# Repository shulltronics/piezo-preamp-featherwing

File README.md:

Piezo Preamp FeatherWing
=========================================

### By Carsten Thue-Bludworth, September 2024

This featherwing provides a high-impedance gain stage and a simple envelope follower for piezo contact microphones.

The piezo is connected via a standard 3.5mm TRS shielded audio connector with the following pinout:
 - Tip: piezo signal
 - Ring: piezo ground
 - Sleeve: cable shield (not connected on piezo end)

The board requires a bipolar +12V/-12V power supply, provided via a 4pos Molex SL connector with the following pinout:
 - 1: +12V
 - 2: GND
 - 3: -12V
 - 4: signal out (default to unattenuated envelope follower signal).

Jumpers and plated holes are provided to configure which signals are sent to which pins.
* By default, the SL connector gets the unattenuated envelope follower signal.
* By default, no analog pins on the feather headers are connected. Use wire jumpers to connect signals to the analog pins you want to use.
* Jumpers can configure the amplifier stage gain, as well as the envelope follower decay time. By default, the gain is 100x and the decay is set with a 270k resistor.

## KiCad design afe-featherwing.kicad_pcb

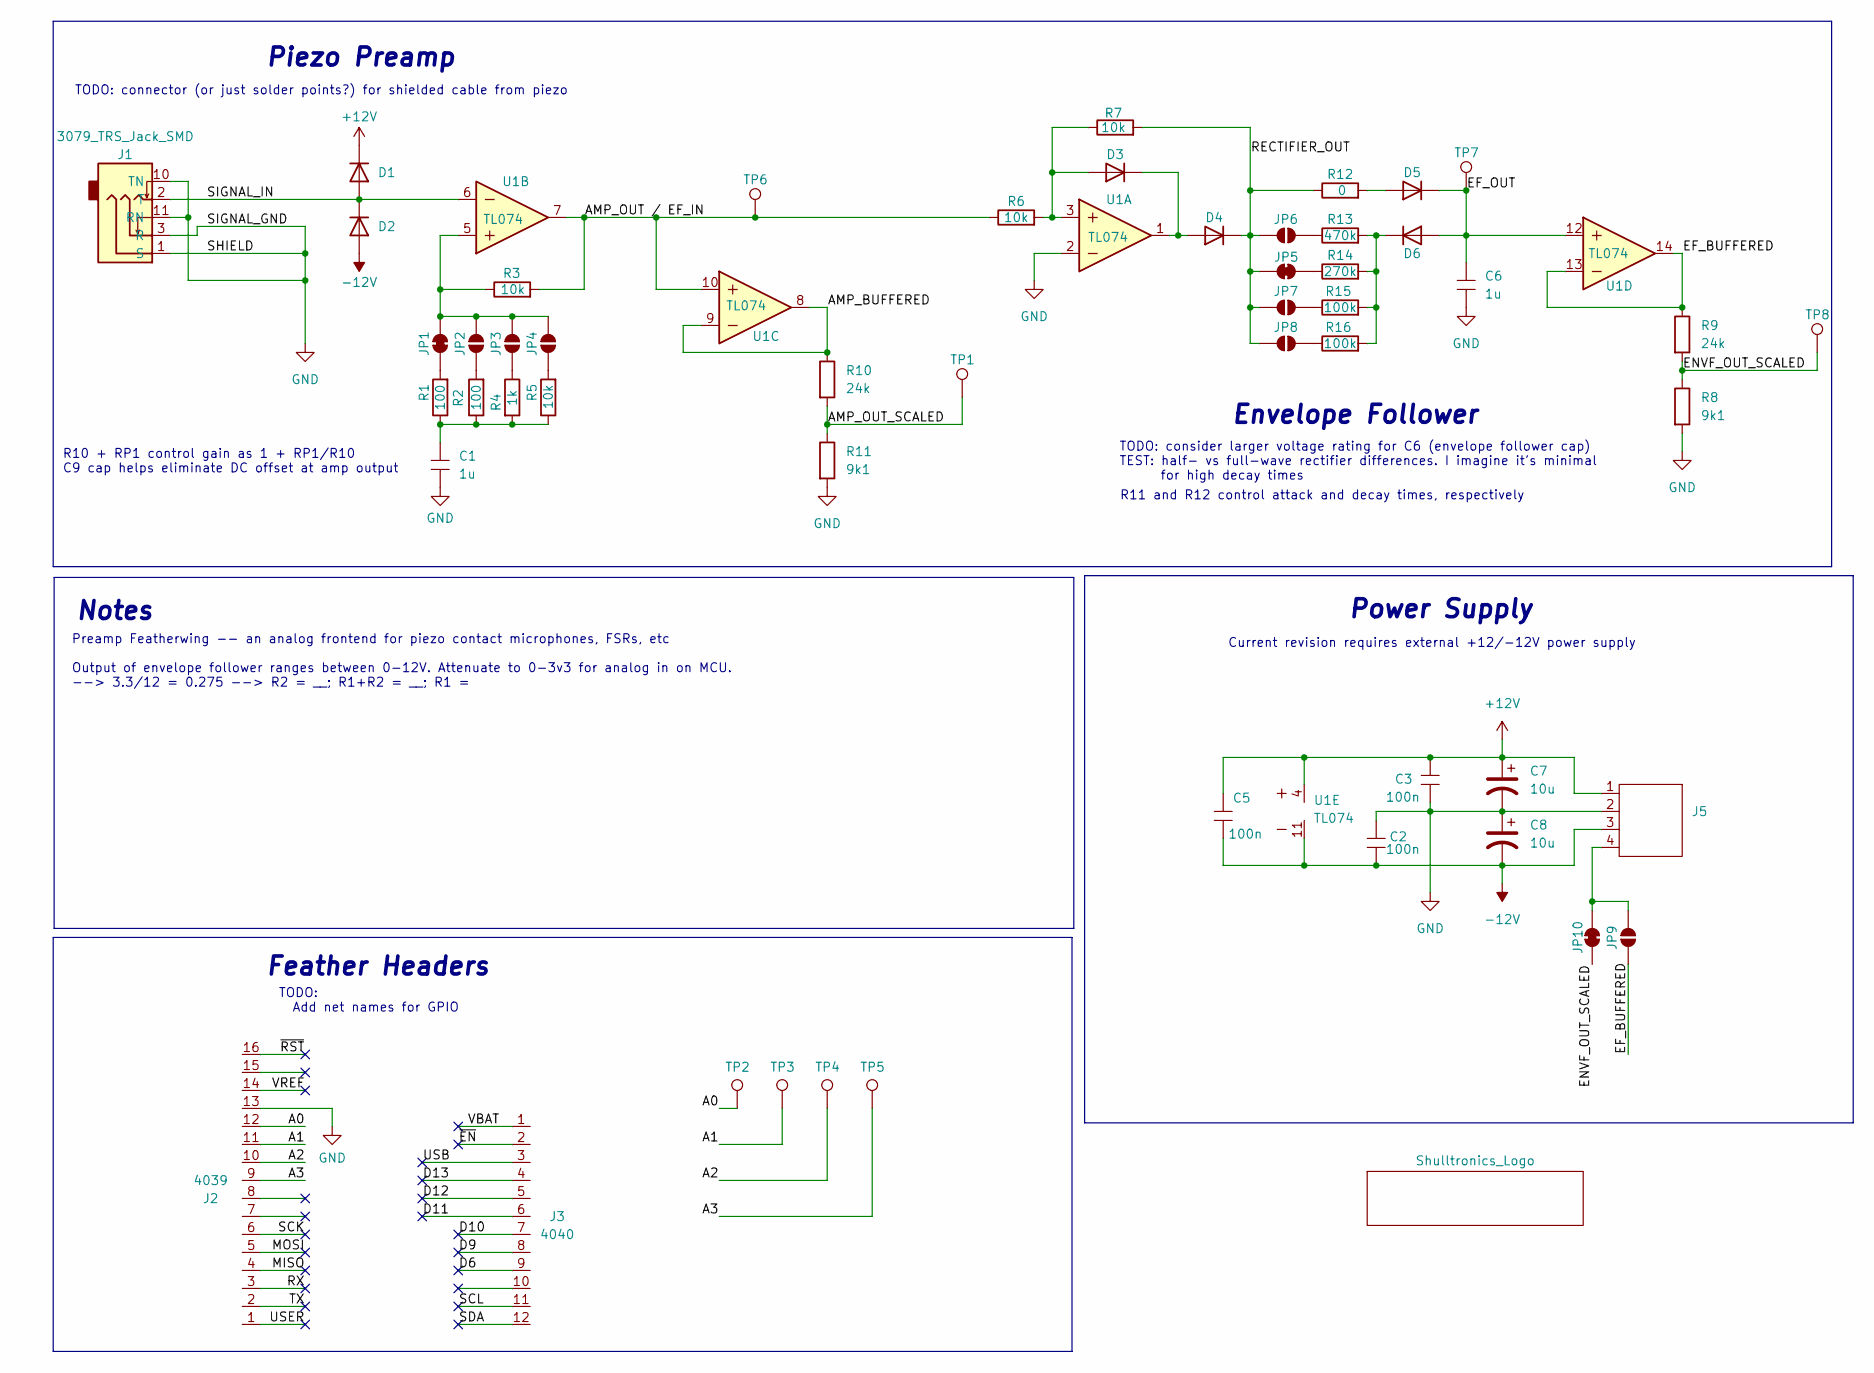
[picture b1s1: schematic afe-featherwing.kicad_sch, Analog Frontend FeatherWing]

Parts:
C1, C6: 4013_Capacitor_1u_16V_0402; C_0402_HandSolder
C2, C3, C5: 3089_Capacitor_100n_16V_0402; C_0402_HandSolder
C7, C8: 4031_Capacitor_10u_35V_SMD; 3088_Capacitor_10u_50V_SMD
D1, D2, D3, D4, D5, D6: 1N4148W; D_SOD-323
J1: 3079_TRS_Jack_SMD
J2: 4039_Header_Male_Vert_16pin_0.1in; 4039_Header_16pos_2.54mm
J3: 4040_Header_Male_Vert_12pin_0.1in; 4040_Header_12pos_2.54mm
J5: 3033_Connector_SL_4pos_RA; 3033_Molex_SL_4pos_RA
JP1: 100; SolderJumper-2_P1.3mm_Bridged_Pad1.0x1.5mm
JP2: 100; SolderJumper-2_P1.3mm_Open_TrianglePad1.0x1.5mm
JP3: 1k; SolderJumper-2_P1.3mm_Open_TrianglePad1.0x1.5mm
JP4: 10k; SolderJumper-2_P1.3mm_Open_TrianglePad1.0x1.5mm
JP5: 270k; SolderJumper-2_P1.3mm_Bridged_Pad1.0x1.5mm
JP6: 470k; SolderJumper-2_P1.3mm_Open_TrianglePad1.0x1.5mm
JP7, JP8: 100k; SolderJumper-2_P1.3mm_Open_TrianglePad1.0x1.5mm
JP9: EF_BUF; SolderJumper-2_P1.3mm_Open_TrianglePad1.0x1.5mm
JP10: EF_ATN; SolderJumper-2_P1.3mm_Bridged_Pad1.0x1.5mm
L1: Shulltronics_Logo
R1, R2: 4038_Resistor_SMD_100_0.125W_1%; RES-0402
R3, R5, R6, R7: 4008_Resistor_SMD_10k_0.125W_1%; RES-0402
R4: 4010_Resistor_SMD_1k_0.125W_1%; RES-0402
R8, R11: 4082_Resistor_SMD_9k1_1/16W_1%; RES-0402
R9, R10: 4083_Resistor_SMD_24k_1/16W_1%; RES-0402
R12: 4021_Resistor_SMD_Jumper; RES-0402
R13: 4080_Resistor_SMD_470k_0.125W_1%; RES-0402
R14: 4019_Resistor_SMD_270k_0.125W_1%; RES-0402
R15, R16: 4017_Resistor_SMD_100k_0.125W_1%_1; RES-0402
TP1: AMP_ATN; TestPoint_THTPad_D1.5mm_Drill0.7mm
TP2: A0; TestPoint_THTPad_D1.5mm_Drill0.7mm
TP3: A1; TestPoint_THTPad_D1.5mm_Drill0.7mm
TP4: A2; TestPoint_THTPad_D1.5mm_Drill0.7mm
TP5: A3; TestPoint_THTPad_D1.5mm_Drill0.7mm
TP6: AMP_OUT; TestPoint_THTPad_D1.5mm_Drill0.7mm
TP7: EF_BUF; TestPoint_THTPad_D1.5mm_Drill0.7mm
TP8: EF_ATN; TestPoint_THTPad_D1.5mm_Drill0.7mm
U1: 3099_TL074CPW_SMD; 3099_TL074CPW_TSSOP14

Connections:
+12V: C3.2, C5.2, C7.1, D1.1 (K), J5.1, U1.4 (VCC)
-12V: C2.1, C5.1, C8.2, D2.2 (A), J5.3, U1.11 (VEE)
/A0: J2.12, TP2.1
/A1: J2.11, TP3.1
/A2: J2.10, TP4.1
/A3: J2.9, TP5.1
/AMP_BUFFERED: R10.1, U1.8 (3OUT), U1.9 (3IN-)
/AMP_OUT / EF_IN: R3.2, R6.1, TP6.1, U1.7 (2OUT), U1.10 (3IN+)
/AMP_OUT_SCALED: R10.2, R11.1, TP1.1
/D6: J3.9
/D9: J3.8
/D10: J3.7
/D11: J3.6
/D12: J3.5
/D13: J3.4
/EF_BUFFERED: JP9.1 (A), R9.1, U1.13 (4IN-), U1.14 (4OUT)
/EF_OUT: C6.2, D5.1 (K), D6.2 (A), TP7.1, U1.12 (4IN+)
/ENVF_OUT_SCALED: JP10.1 (A), R8.1, R9.2, TP8.1
/MISO: J2.4
/MOSI: J2.5
/RECTIFIER_OUT: D4.1 (K), JP5.1 (A), JP6.1 (A), JP7.1 (A), JP8.1 (A), R7.2, R12.1
/RX: J2.3
/SCK: J2.6
/SCL: J3.11
/SDA: J3.12
/SIGNAL_IN: D1.2 (A), D2.1 (K), J1.2 (T), U1.6 (2IN-)
/TX: J2.2
/USB: J3.3
/USER: J2.1
/VBAT: J3.1
/VREF: J2.14
/~EN: J3.2
/~RST: J2.16
GND: C1.1, C2.2, C3.1, C6.1, C7.2, C8.1, J1.1 (S), J1.3 (R), J1.10 (TN), J1.11 (RN), J2.13, J5.2, R8.2, R11.2, U1.2 (1IN-)
unnamed: C1.2, R1.1, R2.1, R4.2, R5.1
unnamed: D3.2 (A), R6.2, R7.1, U1.3 (1IN+)
unnamed: D3.1 (K), D4.2 (A), U1.1 (1OUT)
unnamed: D5.2 (A), R12.2
unnamed: D6.1 (K), R13.2, R14.2, R15.2, R16.2
unnamed: JP1.1 (A), R1.2
unnamed: JP1.2 (B), JP2.2 (B), JP3.2 (B), JP4.2 (B), R3.1, U1.5 (2IN+)
unnamed: JP2.1 (A), R2.2
unnamed: JP3.1 (A), R4.1
unnamed: JP4.1 (A), R5.2
unnamed: JP5.2 (B), R14.1
unnamed: JP6.2 (B), R13.1
unnamed: JP7.2 (B), R15.1
unnamed: JP8.2 (B), R16.1
unnamed: J5.4, JP9.2 (B), JP10.2 (B)

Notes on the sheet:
Notes
TODO: Add net names for GPIO
Envelope Follower
Piezo Preamp
Power Supply
Preamp Featherwing -- an analog frontend for piezo contact microphones, FSRs, etc Output of envelope follower ranges between 0-12V. Attenuate to 0-3v3 for analog in on MCU. --> 3.3/12 = 0.275 --> R2 = __; R1+R2 = __; R1 =
Feather Headers
TODO: consider larger voltage rating for C6 (envelope follower cap) TEST: half- vs full-wave rectifier differences. I imagine it's minimal for high decay times
Current revision requires external +12/-12V power supply
R11 and R12 control attack and decay times, respectively
TODO: connector (or just solder points?) for shielded cable from piezo
R10 + RP1 control gain as 1 + RP1/R10 C9 cap helps eliminate DC offset at amp output

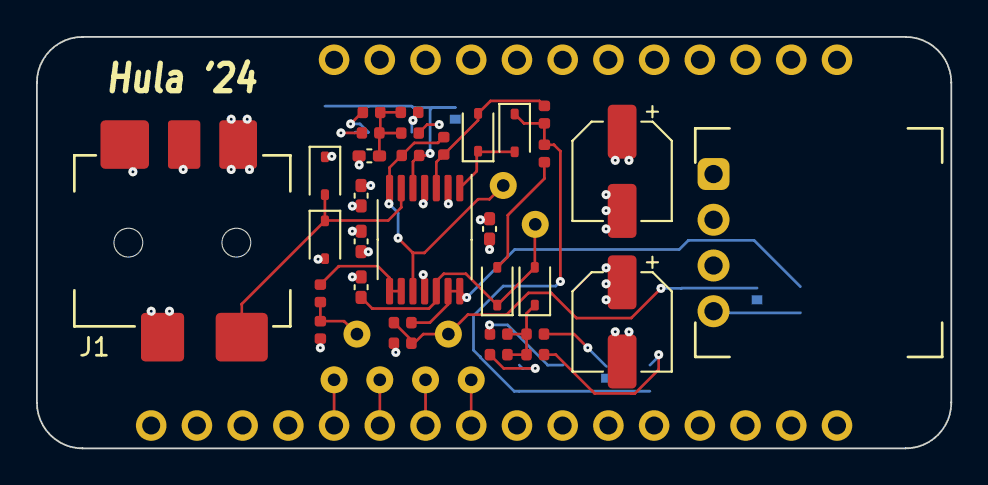
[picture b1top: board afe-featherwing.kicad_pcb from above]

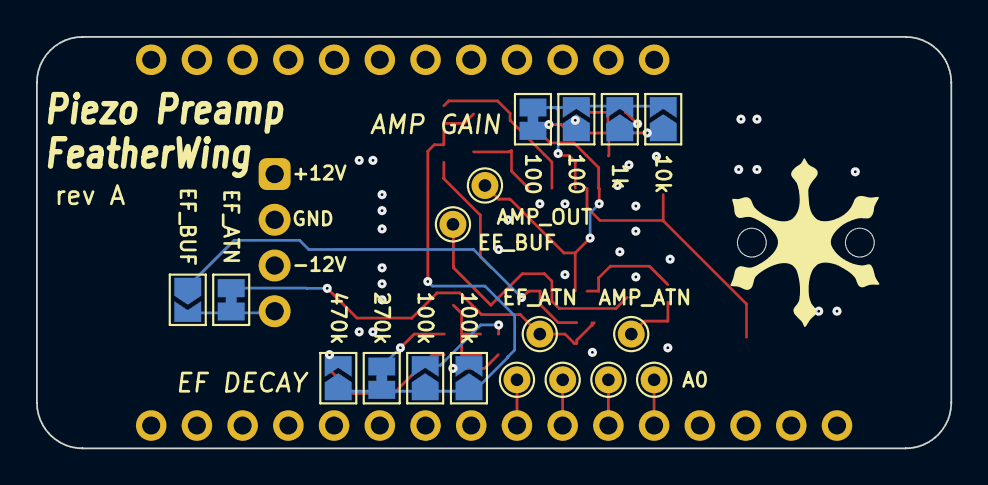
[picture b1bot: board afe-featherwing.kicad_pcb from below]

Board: 4 copper layers, 50.8 x 22.9 mm, 53 parts (18 on the bottom side), 30 nets.

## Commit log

2024-09-24 as ordered for rev A
